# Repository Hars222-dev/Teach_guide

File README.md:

# Teach_guide
A device that teaches directions to children with autism

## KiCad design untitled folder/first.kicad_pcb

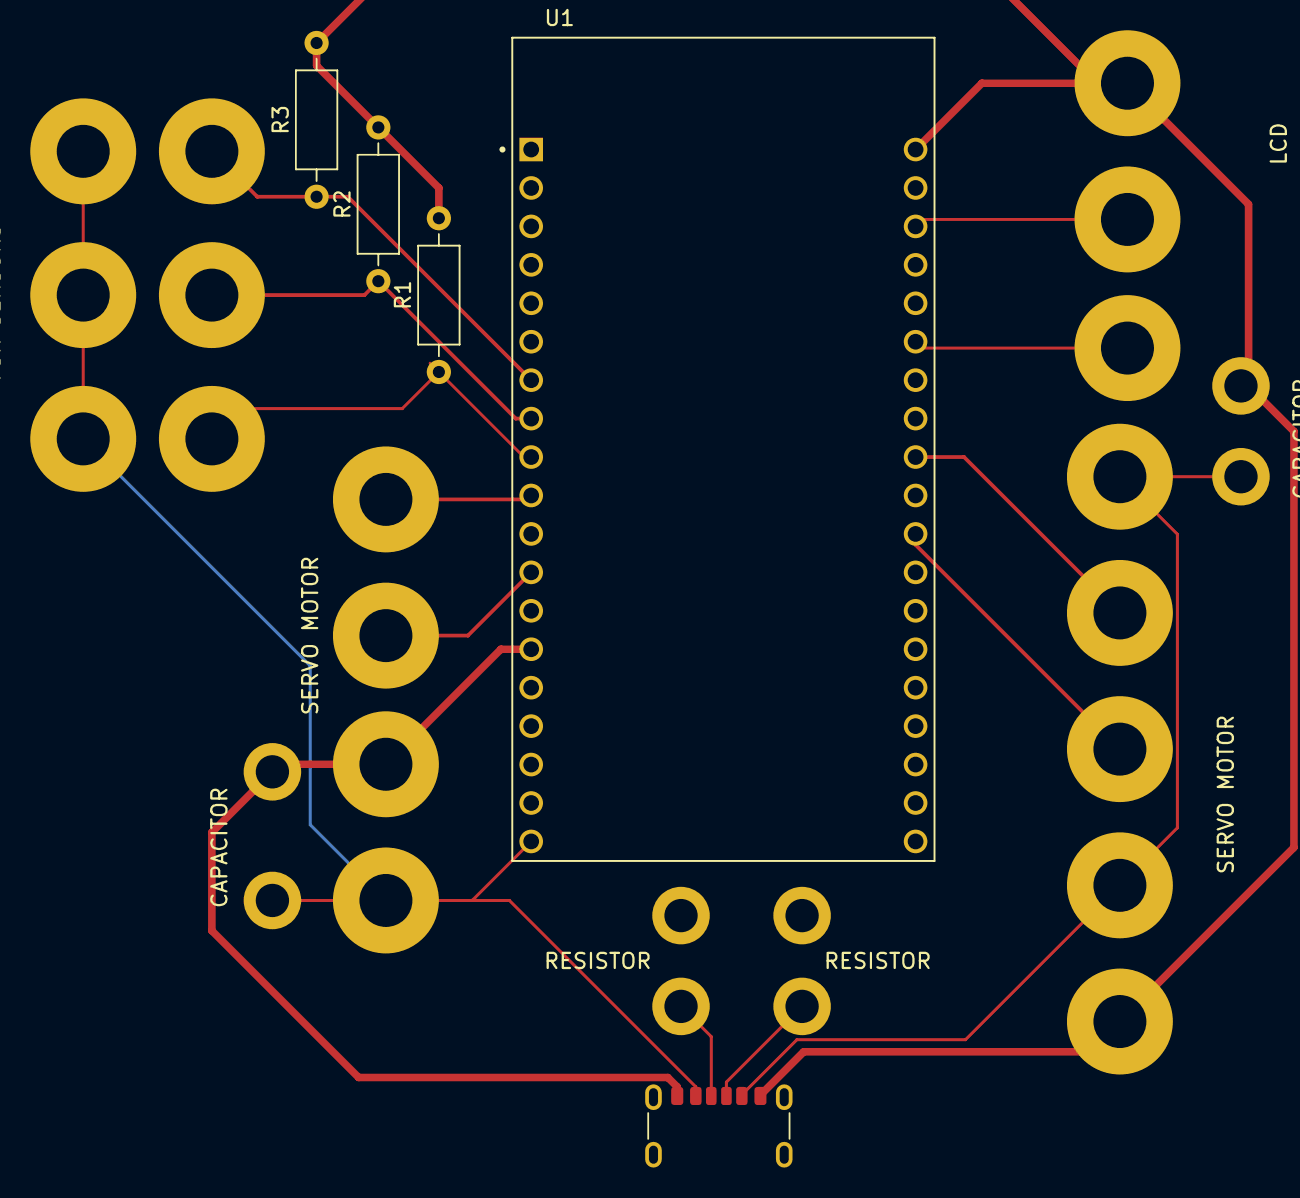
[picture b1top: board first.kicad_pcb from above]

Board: 2 copper layers, 31 parts (0 on the bottom side), 13 nets.

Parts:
5.11K(R+)1, 5.11K(R+)2, 5.11K(R-)1, 5.11K(R-)2: MountingHole_2.2mm_M2_DIN965_Pad
FSR1_Signal1, FSR1_VCC1, FSR2_Signal1, FSR2_VCC1, FSR3_Signal1, FSR3_VCC1: MountingHole_Pad; MountingHole_3.5mm_Pad
J1: USB_C_Receptacle_USB2.0_14P; USB_C_Receptacle_GCT_USB4125-xx-x-0190_6P_TopMnt_Horizontal
LCD_GND1: MountingHole_3.5mm_Pad
LCD_SCL1: MountingHole_3.5mm_Pad
LCD_SDA1: MountingHole_3.5mm_Pad
LCD_VCC1: MountingHole_3.5mm_Pad
R1, R2, R3: 10K; R_Axial_DIN0207_L6.3mm_D2.5mm_P10.16mm_Horizontal
Servo1_GND1, Servo1_VCC1, Servo1_potentiometer1, Servo1_signal1, Servo2_GND1, Servo2_VCC1, Servo2_potentiometer1, Servo2_signal1: MountingHole_3.5mm_Pad
U1: ESP32-DEVKITC-32D; MODULE_ESP32-DEVKITC-32D
capacitor2+1, capacitor2-1: MountingHole_2.2mm_M2_DIN965_Pad
capacitor+1: MountingHole_2.2mm_M2_DIN965_Pad
capacitor-1: MountingHole_2.2mm_M2_DIN965_Pad

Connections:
+5V: FSR1_VCC1.1, FSR2_VCC1.1, FSR3_VCC1.1, J1.A9 (VBUS), J1.B9 (VBUS), LCD_VCC1.1, Servo1_VCC1.1, Servo2_VCC1.1, U1.J2-19 (EXT_5V), capacitor2-1.1, capacitor-1.1
/FSR1_SIGNAL: FSR1_Signal1.1, R3.1, U1.J2-7 (IO32)
/FSR2_SIGNAL: FSR2_Signal1.1, R2.1, U1.J2-8 (IO33)
/FSR3_SIGNAL: FSR3_Signal1.1, R1.1, U1.J2-9 (IO25)
/Ser_Poten: Servo2_potentiometer1.1, U1.J3-9 (IO18)
/ser1_pot: Servo1_potentiometer1.1, U1.J2-10 (IO26)
/ser1_sig: Servo1_signal1.1, U1.J2-12 (IO14)
/ser_sig: Servo2_signal1.1, U1.J3-11 (IO17)
GND: J1.A12 (GND), J1.B12 (GND), LCD_GND1.1, R1.2, R2.2, R3.2, Servo1_GND1.1, Servo2_GND1.1, U1.J2-14 (GND1), U1.J3-1 (GND3), capacitor2+1.1, capacitor+1.1
unnamed: 5.11K(R+)1.1, J1.A5 (CC1)
unnamed: 5.11K(R+)2.1, J1.B5 (CC2)
unnamed: LCD_SCL1.1, U1.J3-6 (IO21)
unnamed: LCD_SDA1.1, U1.J3-3 (IO22)

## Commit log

2025-09-02 PCB files
2025-09-02 organising
